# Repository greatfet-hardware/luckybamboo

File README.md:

# Lucky Bamboo
a quadruple 2.4 GHz ADF7242 transceiver GreatFET neighbor for monitoring Bluetooth LE 

Required KiCad dependency:

https://github.com/greatscottgadgets/gsg-kicad-lib

If you are using git, the preferred way to install gsg-kicad-lib is to use the
submodule:

```
git submodule init && git submodule update
```

## Pin usage

signal  | default pin     | alt1  | alt2
--------|---------|-------|-----
SPORT receive data 1    | J2.36 (SGPIO4)   | J2.18 (SGPIO14) |
SPORT receive data 2    | J1.07 (SGPIO7)   | J1.13 (SGPIO15) |
SPORT receive data 3     | J2.33 (SGPIO6)     | J2.29 (SGPIO7) |
SPORT receive data 4       |    J1.30 (SGPIO3)     | J1.37 (SGPIO13) |
SPORT CLK 1       |     J1.21 (SGPIO8)    |     |
SPORT CLK 2       |    J1.26 (SGPIO9)     |     |
SPORT CLK 3       |    J1.25 (SGPIO10)     |     |
SPORT CLK 4       |    J1.32 (SGPIO11)     |      |
SPI CS 1       |     J2.09    | J2.07 |
SPI CS 2       |     J1.14    | J1.16 |
SPI CS 3       |     J2.31    | J2.24 |
SPI CS 4       |     J1.34    | J1.33 |
SPI CLK       |    J1.38     |     |
SPI SI       |     J1.39    |      |
SPI SO       |    J1.40     |      |
RF switch 1       |   J2.19      |       |
RF switch 2       |    J2.23     |       |
RF switch 3       |    J2.25     |       |
RF switch 4       |    J2.27     |       |
IRQ1 1       |   2x4 header      |   J2.15    |
IRQ1 2       |    2x4 header     |   J1.18     |
IRQ1 3       |    2x4 header     |    J2.34   |
IRQ1 4       |    2x4 header     |   J1.35    |
IRQ2/TRFS 1       |   2x4 header      | J2.16      |
IRQ2/TRFS 2       |    2x4 header     |   J1.3    |
IRQ2/TRFS 3       |    2x4 header     |    J2.35   |
IRQ2/TRFS 4       |    2x4 header     |   J1.28    |

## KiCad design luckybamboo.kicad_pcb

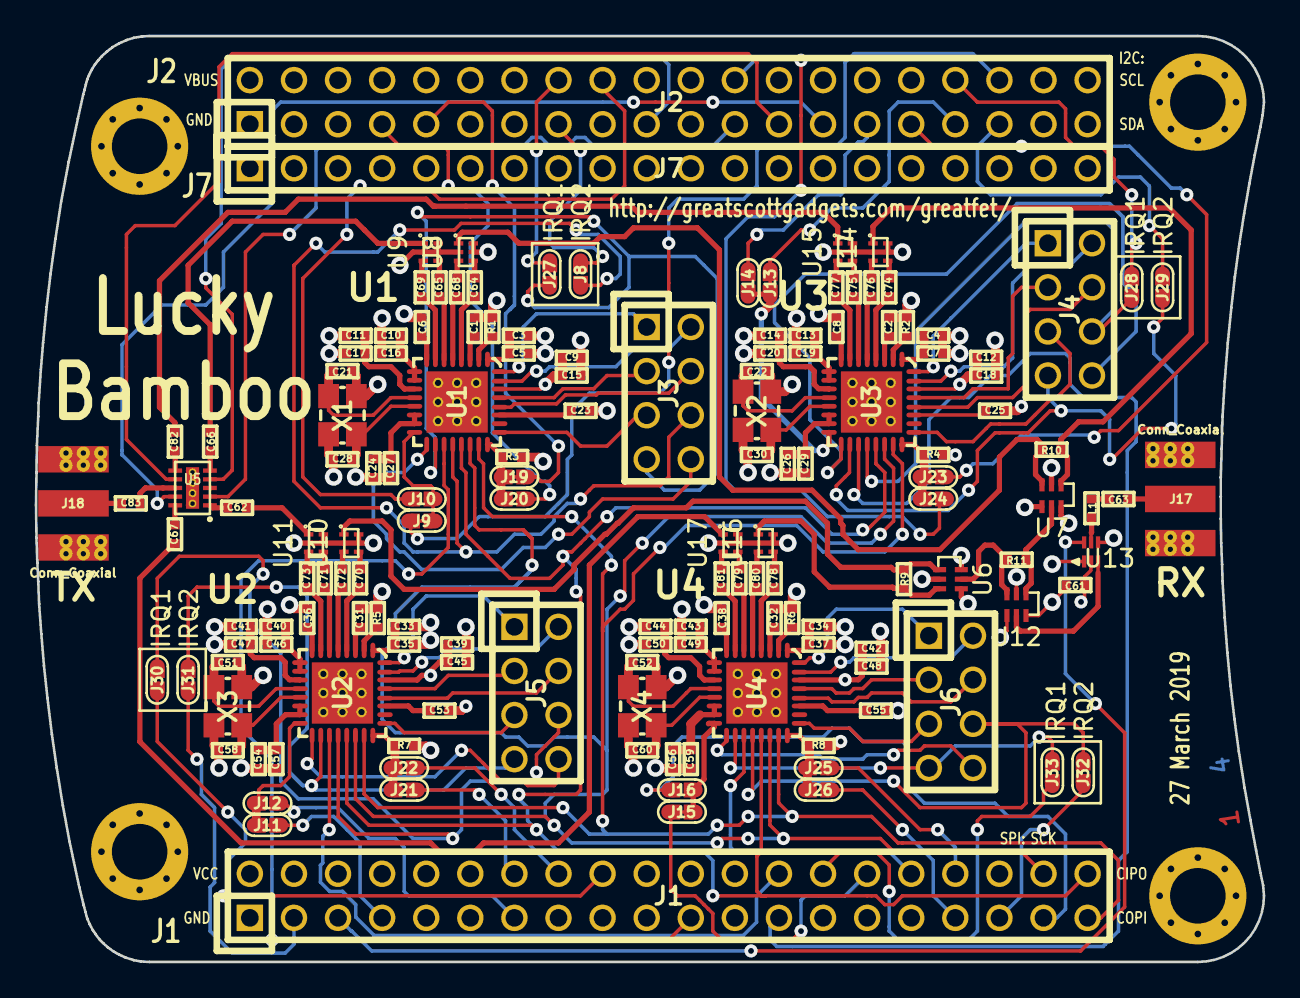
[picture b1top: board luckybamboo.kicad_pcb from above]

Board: 4 copper layers, 70.7 x 53.3 mm, 153 parts (0 on the bottom side), 162 nets.

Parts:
C1, C2, C6, C8, C31, C32, C36, C38: 100pF; 0402
C3, C4, C9, C10, C11, C12, C13, C14, C24, C26, C33, C34, C39, C40, C41, C42, C43, C44, C54, C56: 220nF; 0402
C5, C7, C15, C16, C17, C18, C19, C20, C27, C29, C35, C37, C45, C46, C47, C48, C49, C50, C57, C59: 27pF; 0402
C21, C22, C28, C30, C51, C52, C58, C60: 18pF; 0402
C23, C25, C53, C55, C61, C63: 1nF; 0402
C62, C66, C67, C82, C83: 47pF; 0402
C64, C65, C68, C69, C70, C71, C72, C73, C74, C75, C76, C77, C78, C79, C80, C81: 10nF; 0402
J1: NEIGHBOR1; HEADER-2x20
J2: NEIGHBOR2; HEADER-2x20
J3, J4, J5, J6: Conn_01x08; HEADER-2x4
J7: BONUS_ROW; HEADER-1x20
J8, J9, J10, J11, J12, J13, J14, J15, J16, J19, J20, J21, J22, J23, J24, J25, J26, J27, J28, J29, J30, J31, J32, J33: TEST_2P; 0603-JUMPER
J17, J18: Conn_Coaxial; SMA-EDGE
L1: 3.8nH; 0402
MH1, MH2, MH3, MH4: MOUNTING_HOLE; HOLE126MIL-COPPER
R1, R2, R5, R6: 27k; 0402
R3, R4, R7, R8: 10k; 0402
R9, R10, R11: 100; 0402
U1, U2, U3, U4: ADF7242; LFCSP32
U5: SKY13322; SKY13322-375LF
U6, U7, U12: HHM2293A1
U8, U9, U10, U11, U14, U15, U16, U17: ADF7242_balun
U13: BGA7H1N6
X1, X2, X3, X4: XTAL4PIN; XTAL3.2x2.5mm

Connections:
/DR1: J2.36, J9.1, J9.2, J10.1, U1.16
/DR2: J1.7, J11.1, J11.2, J12.1, U2.16
/DR3: J2.33, J13.1, J13.2, J14.1, U3.16
/DR4: J1.30, J15.1, J15.2, J16.1, U4.16
/DT1: J3.8, U1.17
/DT2: J5.8, U2.17
/DT3: J4.8, U3.17
/DT4: J6.8, U4.17
/IRQ1: J3.6, J8.2, U1.20
/IRQ2: J5.6, J30.2, U2.20
/IRQ3: J4.6, J28.2, U3.20
/IRQ4: J6.6, J32.2, U4.20
/P1_3: J1.40, U1.21, U2.21, U3.21, U4.21
/P1_4: J1.39, U1.23, U2.23, U3.23, U4.23
/P1_5: J1.13, J12.2
/P1_6: J1.16, J22.2
/P1_8: J1.18, J30.1
/P1_12: J1.21, U1.19
/P1_13: J1.26, U2.19
/P1_14: J1.25, U3.19
/P1_15: J1.28, J33.1
/P1_17: J1.32, U4.19
/P1_19: J1.38, U1.22, U2.22, U3.22, U4.22
/P1_20: J1.37, J16.2
/P2_0: J1.35, J32.1
/P2_1: J2.35, J29.1
/P2_4: J2.19, U5.4
/P2_5: J2.18, J10.2
/P2_6: J2.15, J8.1
/P3_1: J2.24, J24.2
/P4_3: J2.9, J19.1, J19.2, J20.1, R3.2, U1.24
/P4_4: J2.7, J20.2
/P4_9: J1.3, J31.1
/P4_10: J1.5, U13.6
/P5_2: J1.14, J21.1, J21.2, J22.1, R7.2, U2.24
/P6_6: J2.34, J28.1
/P6_7: J2.31, J23.1, J23.2, J24.1, R4.2, U3.24
/P6_8: J2.29, J14.2
/P7_0: J2.27, U5.9
/P7_1: J2.25, U5.7
/P7_2: J2.23, U5.2
/P7_7: J2.16, J27.1
/P9_5: J1.33, J26.2
/P9_6: J1.34, J25.1, J25.2, J26.1, R8.2, U4.24
/PABIAOP1: J3.1, U1.32
/PABIAOP2: J5.1, U2.32
/PABIAOP3: J4.1, U3.32
/PABIAOP4: J6.1, U4.32
/PAVSUP1: J3.2, U1.31
/PAVSUP2: J5.2, U2.31
/PAVSUP3: J4.2, U3.31
/PAVSUP4: J6.2, U4.31
/RFIN: L1.1, U13.5
/RFIN1: R10.1, U7.3, U8.1
/RFIN1_N: C68.2, U1.5
/RFIN1_P: C64.2, U1.4
/RFIN2: R9.2, U6.1, U10.1
/RFIN2_N: C72.2, U2.5
/RFIN2_P: C70.2, U2.4
/RFIN3: R10.2, U7.1, U14.1
/RFIN3_N: C76.2, U3.5
/RFIN3_P: C74.2, U3.4
/RFIN4: R9.1, U6.3, U16.1
/RFIN4_N: C80.2, U4.5
/RFIN4_P: C78.2, U4.4
/RFOUT1: C66.2, U9.1
/RFOUT1_N: C69.2, U1.7
/RFOUT1_P: C65.2, U1.6
/RFOUT2: C62.1, U11.1
/RFOUT2_N: C73.2, U2.7
/RFOUT2_P: C71.2, U2.6
/RFOUT3: C82.1, U15.1
/RFOUT3_N: C77.2, U3.7
/RFOUT3_P: C75.2, U3.6
/RFOUT4: C67.2, U17.1
/RFOUT4_N: C81.2, U4.7
/RFOUT4_P: C79.2, U4.6
/TRFS1: J3.7, J27.2, U1.18
/TRFS2: J5.7, J31.2, U2.18
/TRFS3: J4.7, J29.2, U3.18
/TRFS4: J6.7, J33.2, U4.18
/TXEN1: J3.5, U1.25
/TXEN2: J5.5, U2.25
/TXEN3: J4.5, U3.25
/TXEN4: J6.5, U4.25
/XOSC32KN1: J3.3, U1.29
/XOSC32KN2: J5.3, U2.29
/XOSC32KN3: J4.3, U3.29
/XOSC32KN4: J6.3, U4.29
/XOSC32KP1: J3.4, U1.28
/XOSC32KP2: J5.4, U2.28
/XOSC32KP3: J4.4, U3.28
/XOSC32KP4: J6.4, U4.28
GND: C1.1, C2.1, C3.1, C4.1, C5.1, C6.2, C7.1, C8.2, C9.1, C10.2, C11.2, C12.1, C13.2, C14.2, C15.1, C16.2, C17.2, C18.1, C19.2, C20.2, C21.2, C22.2, C23.1, C24.2, C25.1, C26.2, C27.2, C28.2, C29.2, C30.2, C31.1, C32.1, C33.1, C34.1, C35.1, C36.2, C37.1, C38.2, C39.1, C40.2, C41.2, C42.1, C43.2, C44.2, C45.1, C46.2, C47.2, C48.1, C49.2, C50.2, C51.2, C52.2, C53.1, C54.2, C55.1, C56.2, C57.2, C58.2, C59.2, C60.2, C61.1, J1.1, J2.1, J7.1, J7.10, J7.19, J17.2, J18.2, MH1.1, MH2.1, MH3.1, MH4.1, R1.1, R2.1, R5.1, R6.1, U1.0, U2.0, U3.0, U4.0, U5.0, U6.2, U6.4, U6.6, U7.2, U7.4, U7.6, U8.2, U8.5, U8.6, U9.2, U9.5, U9.6, U10.2, U10.5, U10.6, U11.2, U11.5, U11.6, U12.2, U12.4, U12.6, U13.1, U13.4, U14.2, U14.5, U14.6, U15.2, U15.5, U15.6, U16.2, U16.5, U16.6, U17.2, U17.5, U17.6, X1.2, X1.4, X2.2, X2.4, X3.2, X3.4, X4.2, X4.4
unnamed: C1.2, U1.3
unnamed: C2.2, U3.3
unnamed: C3.2, C5.2, U1.1
unnamed: C4.2, C7.2, U3.1
unnamed: C6.1, U1.8
unnamed: C8.1, U3.8
unnamed: C10.1, C16.1, U1.9, U1.10
unnamed: C11.1, C17.1, U1.11
unnamed: C13.1, C19.1, U3.9, U3.10
unnamed: C14.1, C20.1, U3.11
unnamed: C21.1, U1.12, X1.1
unnamed: C22.1, U3.12, X2.1
unnamed: C23.2, U1.27
unnamed: C24.1, C27.1, U1.14, U1.15
unnamed: C25.2, U3.27
unnamed: C26.1, C29.1, U3.14, U3.15
unnamed: C28.1, U1.13, X1.3
unnamed: C30.1, U3.13, X2.3
unnamed: C31.2, U2.3
unnamed: C32.2, U4.3
unnamed: C33.2, C35.2, U2.1
unnamed: C34.2, C37.2, U4.1
unnamed: C36.1, U2.8
unnamed: C38.1, U4.8
unnamed: C40.1, C46.1, U2.9, U2.10
unnamed: C41.1, C47.1, U2.11
unnamed: C43.1, C49.1, U4.9, U4.10
unnamed: C44.1, C50.1, U4.11
unnamed: C51.1, U2.12, X3.1
unnamed: C52.1, U4.12, X4.1
unnamed: C53.2, U2.27
unnamed: C54.1, C57.1, U2.14, U2.15
unnamed: C55.2, U4.27
unnamed: C56.1, C59.1, U4.14, U4.15
unnamed: C58.1, U2.13, X3.3
unnamed: C60.1, U4.13, X4.3
unnamed: C62.2, U5.1
unnamed: C63.1, L1.2
unnamed: C63.2, J17.1
unnamed: C64.1, U8.4
unnamed: C65.1, U9.4
unnamed: C66.1, U5.5
unnamed: C67.1, U5.10
unnamed: C68.1, U8.3
unnamed: C69.1, U9.3
unnamed: C70.1, U10.4
unnamed: C71.1, U11.4
unnamed: C72.1, U10.3
unnamed: C73.1, U11.3
unnamed: C74.1, U14.4
unnamed: C75.1, U15.4
unnamed: C76.1, U14.3
unnamed: C77.1, U15.3
unnamed: C78.1, U16.4
unnamed: C79.1, U17.4
unnamed: C80.1, U16.3
unnamed: C81.1, U17.3
unnamed: C82.2, U5.6
unnamed: C83.1, U5.8
unnamed: C83.2, J18.1
unnamed: R1.2, U1.2
unnamed: R2.2, U3.2
unnamed: R5.2, U2.2
unnamed: R6.2, U4.2
unnamed: R11.1, U6.5, U12.3
unnamed: R11.2, U7.5, U12.1
unnamed: U12.5, U13.3
VCC: C9.2, C12.2, C15.2, C18.2, C39.2, C42.2, C45.2, C48.2, C61.2, J1.2, J7.20, R3.1, R4.1, R7.1, R8.1, U1.30, U2.30, U3.30, U4.30, U13.2

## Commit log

2019-05-27 split luckybamboo into separate repository
2019-05-27 updated README.md to be luckybamboo-specific
2019-09-06 move information from greatfet wiki to README
2020-07-03 adopt OSHWA convention for SPI signal names https://www.oshwa.org/a-resolution-to-redefine-spi-signal-names
